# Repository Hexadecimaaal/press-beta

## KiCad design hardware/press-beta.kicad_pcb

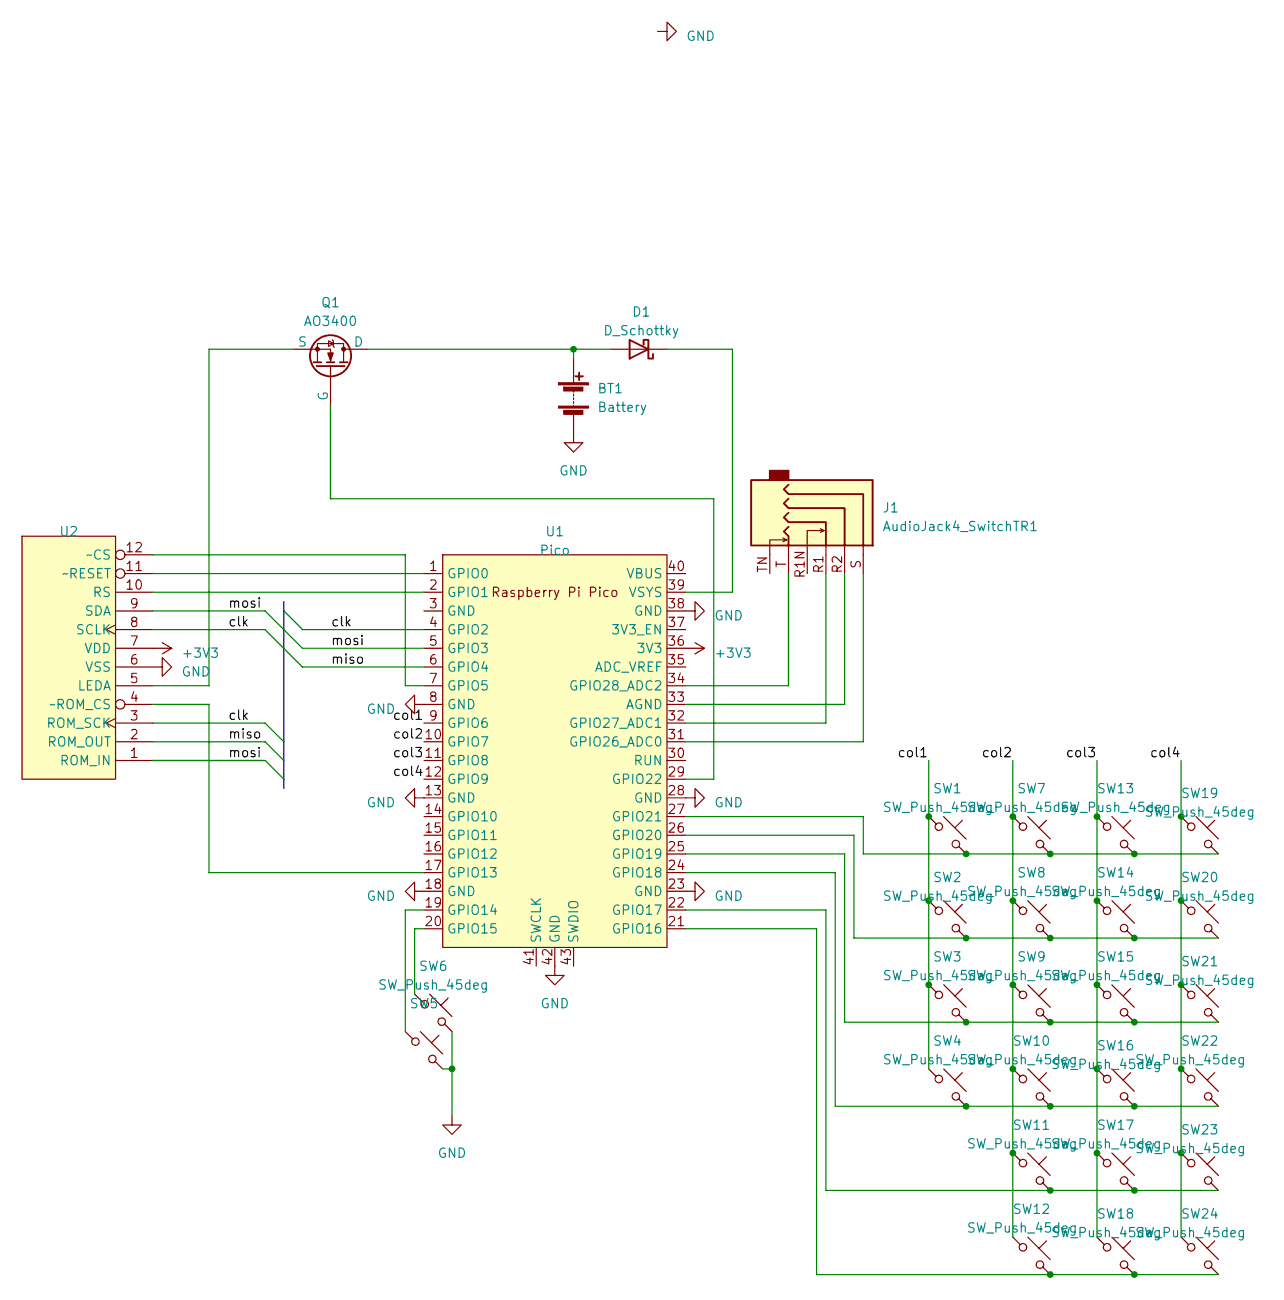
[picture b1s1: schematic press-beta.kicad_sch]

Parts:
BT1: Battery; SolderWire-0.75sqmm_1x02_P4.8mm_D1.25mm_OD2.3mm
D1: D_Schottky; D_SMA_Handsoldering
J1: AudioJack4_SwitchTR1; Jack_3.5mm_PJ311_Horizontal
Q1: AO3400; SOT-23_Handsoldering
SW1, SW2, SW3, SW4, SW5, SW6, SW7, SW8, SW9, SW10, SW11, SW12, SW13, SW14, SW15, SW16, SW17, SW18, SW19, SW20, SW21, SW22, SW23, SW24: SW_Push_45deg; tactile_switch_6x6x5
U1: Pico; RPi_Pico_SMD_TH
U2: LCD_nopost

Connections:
+3V3: U1.36 (3V3), U2.7 (VDD)
/clk: U1.4 (GPIO2), U2.3 (ROM_SCK), U2.8 (SCLK)
/col1: SW1.1, SW2.1, SW3.1, SW4.1, U1.9 (GPIO6)
/col2: SW7.1, SW8.1, SW9.1, SW10.1, SW11.1, SW12.1, U1.10 (GPIO7)
/col3: SW13.1, SW14.1, SW15.1, SW16.1, SW17.1, SW18.1, U1.11 (GPIO8)
/col4: SW19.1, SW20.1, SW21.1, SW22.1, SW23.1, SW24.1, U1.12 (GPIO9)
/miso: U1.6 (GPIO4), U2.2 (ROM_OUT)
/mosi: U1.5 (GPIO3), U2.1 (ROM_IN), U2.9 (SDA)
GND: BT1.2 (-), SW5.2, SW6.2, U1.8 (GND), U1.13 (GND), U1.18 (GND), U1.23 (GND), U1.28 (GND), U1.38 (GND), U1.42 (GND), U2.6 (VSS)
unnamed: BT1.1 (+), D1.2 (A), Q1.1 (D)
unnamed: D1.1 (K), U1.39 (VSYS)
unnamed: Q1.2 (G), U1.29 (GPIO22)
unnamed: Q1.3 (S), U2.5 (LEDA)
unnamed: J1.R2, U1.33 (AGND)
unnamed: U1.1 (GPIO0), U2.11 (~RESET)
unnamed: U1.2 (GPIO1), U2.10 (RS)
unnamed: U1.7 (GPIO5), U2.12 (~CS)
unnamed: U1.17 (GPIO13), U2.4 (~ROM_CS)
unnamed: SW5.1, U1.19 (GPIO14)
unnamed: SW6.1, U1.20 (GPIO15)
unnamed: SW12.2, SW18.2, SW24.2, U1.21 (GPIO16)
unnamed: SW11.2, SW17.2, SW23.2, U1.22 (GPIO17)
unnamed: SW4.2, SW10.2, SW16.2, SW22.2, U1.24 (GPIO18)
unnamed: SW3.2, SW9.2, SW15.2, SW21.2, U1.25 (GPIO19)
unnamed: SW2.2, SW8.2, SW14.2, SW20.2, U1.26 (GPIO20)
unnamed: SW1.2, SW7.2, SW13.2, SW19.2, U1.27 (GPIO21)
unnamed: J1.S, U1.31 (GPIO26_ADC0)
unnamed: J1.R1, U1.32 (GPIO27_ADC1)
unnamed: J1.T, U1.34 (GPIO28_ADC2)

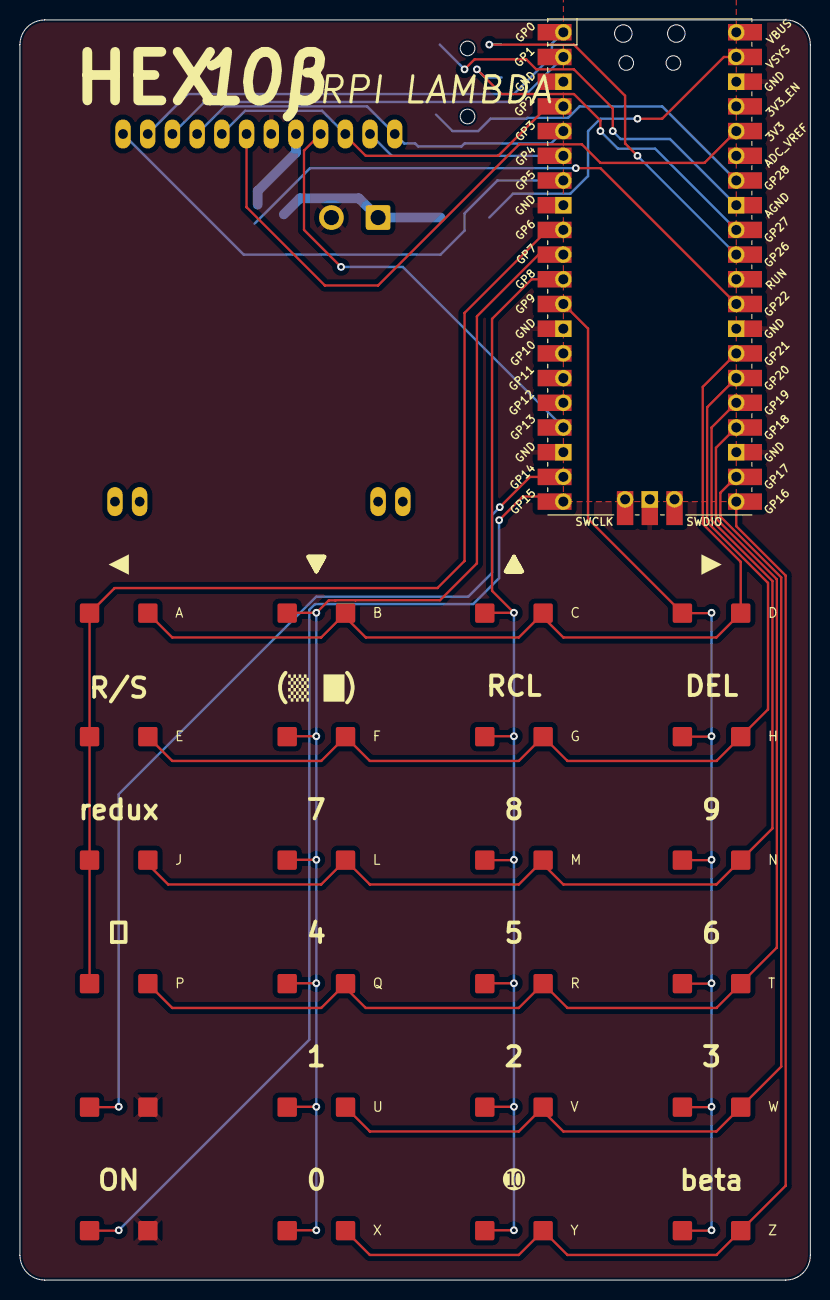
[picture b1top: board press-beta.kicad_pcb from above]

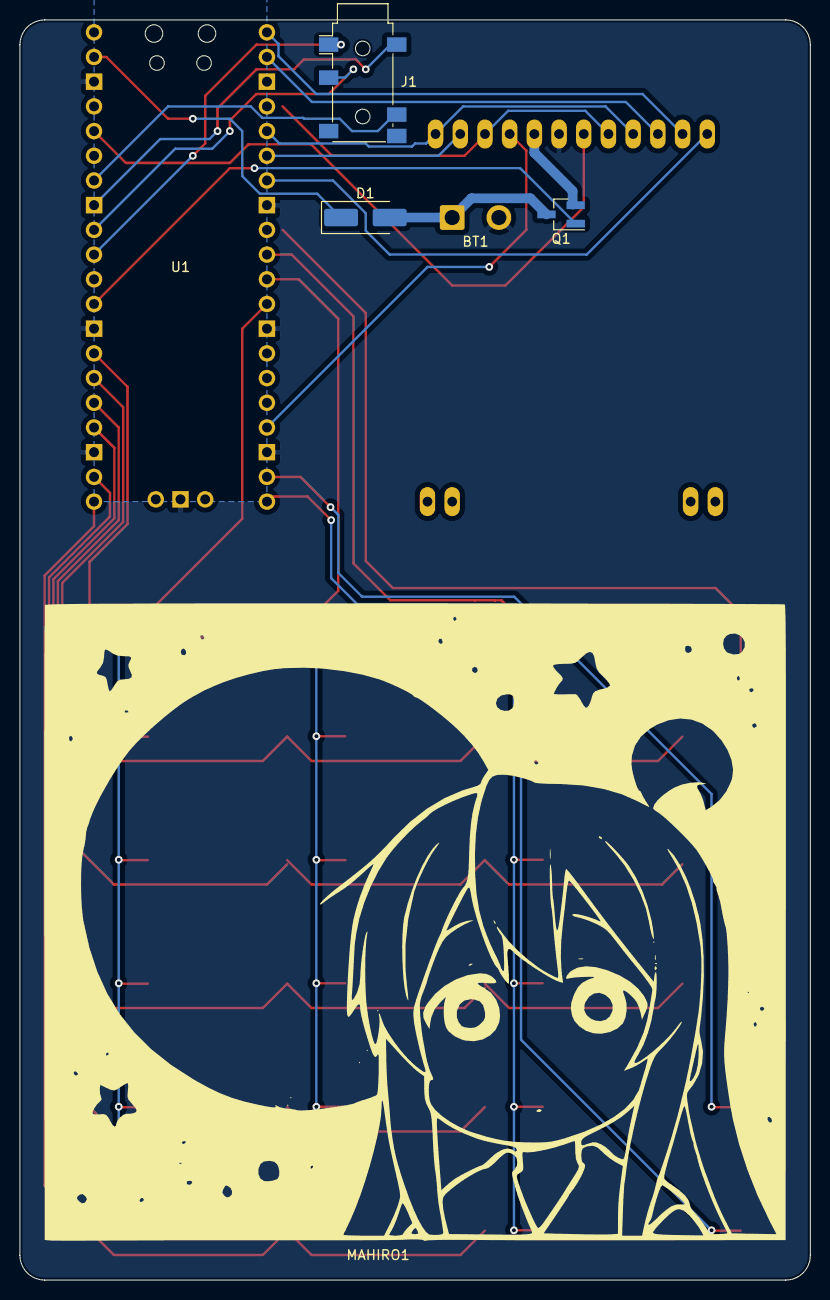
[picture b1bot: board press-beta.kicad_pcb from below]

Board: 2 copper layers, 81.3 x 129.6 mm, 30 parts (3 on the bottom side), 29 nets.

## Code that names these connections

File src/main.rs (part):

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
  // let mut led_pin = pins.gpio25.into_push_pull_output();

  let _ = pins.gpio2.into_mode::<FunctionSpi>();
  let _ = pins.gpio3.into_mode::<FunctionSpi>();
  let _ = pins.gpio4.into_mode::<FunctionSpi>();

  let mut lcd = lcd::Lcd::new(
    pins.gpio0,
    pins.gpio5,
    pins.gpio1,
    hal::spi::Spi::<_, _, 8>::new(pac.SPI0),
    &mut pac.RESETS,
  );
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
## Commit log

2023-04-30 lambda
2023-05-19 up/down works now
2023-05-20 slot + edit logic
2023-05-20 shift + leaf mode + formatting
2023-05-30 big refactor
2023-05-30 update flake; remove box
2023-05-31 start hardware side
2023-06-06 start on pico
2023-06-06 lcd works yay
2023-06-07 pcb mod
2023-06-24 lcd working pretty well now
2023-07-11 first hardware iteration?
2023-07-14 fix lambda once again qaq
2023-12-03 move dir + update rp2040
2023-12-04 embedded graphics driver
2023-12-21 becoming the garbage collector
